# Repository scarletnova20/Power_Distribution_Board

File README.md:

# Power Distribution Board

Four-layer, 42 x 42 mm power distribution board for a 4S2P Li-ion system. The design combines a high-current ESC supply path, reverse-polarity protection, 5 V and 12 V auxiliary power interfaces, and analog/digital power telemetry.

> [!CAUTION]
> **This project is not fabrication-ready, and 50 A is a design target—not a tested current rating.** The current revision requires a non-standard mixed-copper stackup that has not been accepted by a fabricator. Thermal performance, current sharing, fuse coordination, wiring, BEC selection, and full-load operation also remain unqualified. Do not order boards or connect a high-current battery without completing the open release gates.

## Current design

The authoritative revision is in [`engineering/release50`](engineering/release50/):

- [`PDB_50A.kicad_pro`](engineering/release50/PDB_50A.kicad_pro) — KiCad project
- [`PDB_50A.kicad_sch`](engineering/release50/PDB_50A.kicad_sch) — schematic
- [`PDB_50A.kicad_pcb`](engineering/release50/PDB_50A.kicad_pcb) — PCB layout
- [`PDB_50A.kicad_dru`](engineering/release50/PDB_50A.kicad_dru) — design rules
- [`CONTINUATION.md`](engineering/release50/CONTINUATION.md) — latest engineering status and revision history
- [`fabrication_20260915/MANUFACTURING_SPEC.md`](engineering/release50/fabrication_20260915/MANUFACTURING_SPEC.md) — current vendor-neutral manufacturing requirements
- [`PDB_50A_DESIGN_RECORD.md`](engineering/release50/PDB_50A_DESIGN_RECORD.md) — detailed design record, interfaces, BOM review, and release gates

The root-level `Swayatt_PCB*` files and `engineering/release42` are earlier development revisions and are retained for traceability.

## Design summary

| Item | Current design |
| --- | --- |
| Board | 42 x 42 mm, nominal 1.6 mm, four copper layers |
| Battery | 4S2P Li-ion; 14.8 V nominal, 16.8 V maximum normal |
| Load target | 50 A aggregate, unqualified |
| Stackup | 1 oz outer / 2 oz inner copper; vendor acceptance required |
| Main protection | External fuse provision and LM74502-controlled parallel NMOS reverse-polarity stage |
| Main output | ESC battery interface |
| Auxiliary power | External 5 V and 12 V BEC interfaces; outputs must not be paralleled |
| Telemetry | INA169 analog current sensing and INA228 digital power monitoring |
| CAD format | KiCad 10.0 |

## Verification snapshot

The active September 15, 2026 revision records:

- zero ERC findings and zero unconnected items;
- zero DRC findings under the included 6 mil / 5 mil mixed-copper rule deck;
- 52 electrical invariants and nine additional checks passing;
- matching PCB/netlist pad assignments and verified manufacturing exports.

These checks establish internal design consistency only. They do **not** establish manufacturability, thermal safety, a 50 A rating, or production readiness. See [`verification.json`](engineering/release50/verification.json) and the latest status in [`CONTINUATION.md`](engineering/release50/CONTINUATION.md).

## Opening the project

1. Install KiCad 10.0 or a compatible newer version.
2. Clone this repository.
3. Open `engineering/release50/PDB_50A.kicad_pro`.
4. Keep the repository structure intact so the included symbol and footprint library tables resolve correctly.

Before modifying or exporting the board, read the latest continuation notes and manufacturing specification. Generated review packages are evidence artifacts, not approved fabrication releases.

## Repository layout

```text
engineering/release50/   Active 50 A-target design, checks, and review outputs
engineering/release42/   Previous 42 mm development revision
engineering/             Analysis, routing, rendering, and verification scripts
Swayatt_Local.pretty/    Project-specific KiCad footprints
Swayatt_Local.kicad_sym  Project-specific KiCad symbols
```

## License

Licensed under the [Apache License 2.0](LICENSE).

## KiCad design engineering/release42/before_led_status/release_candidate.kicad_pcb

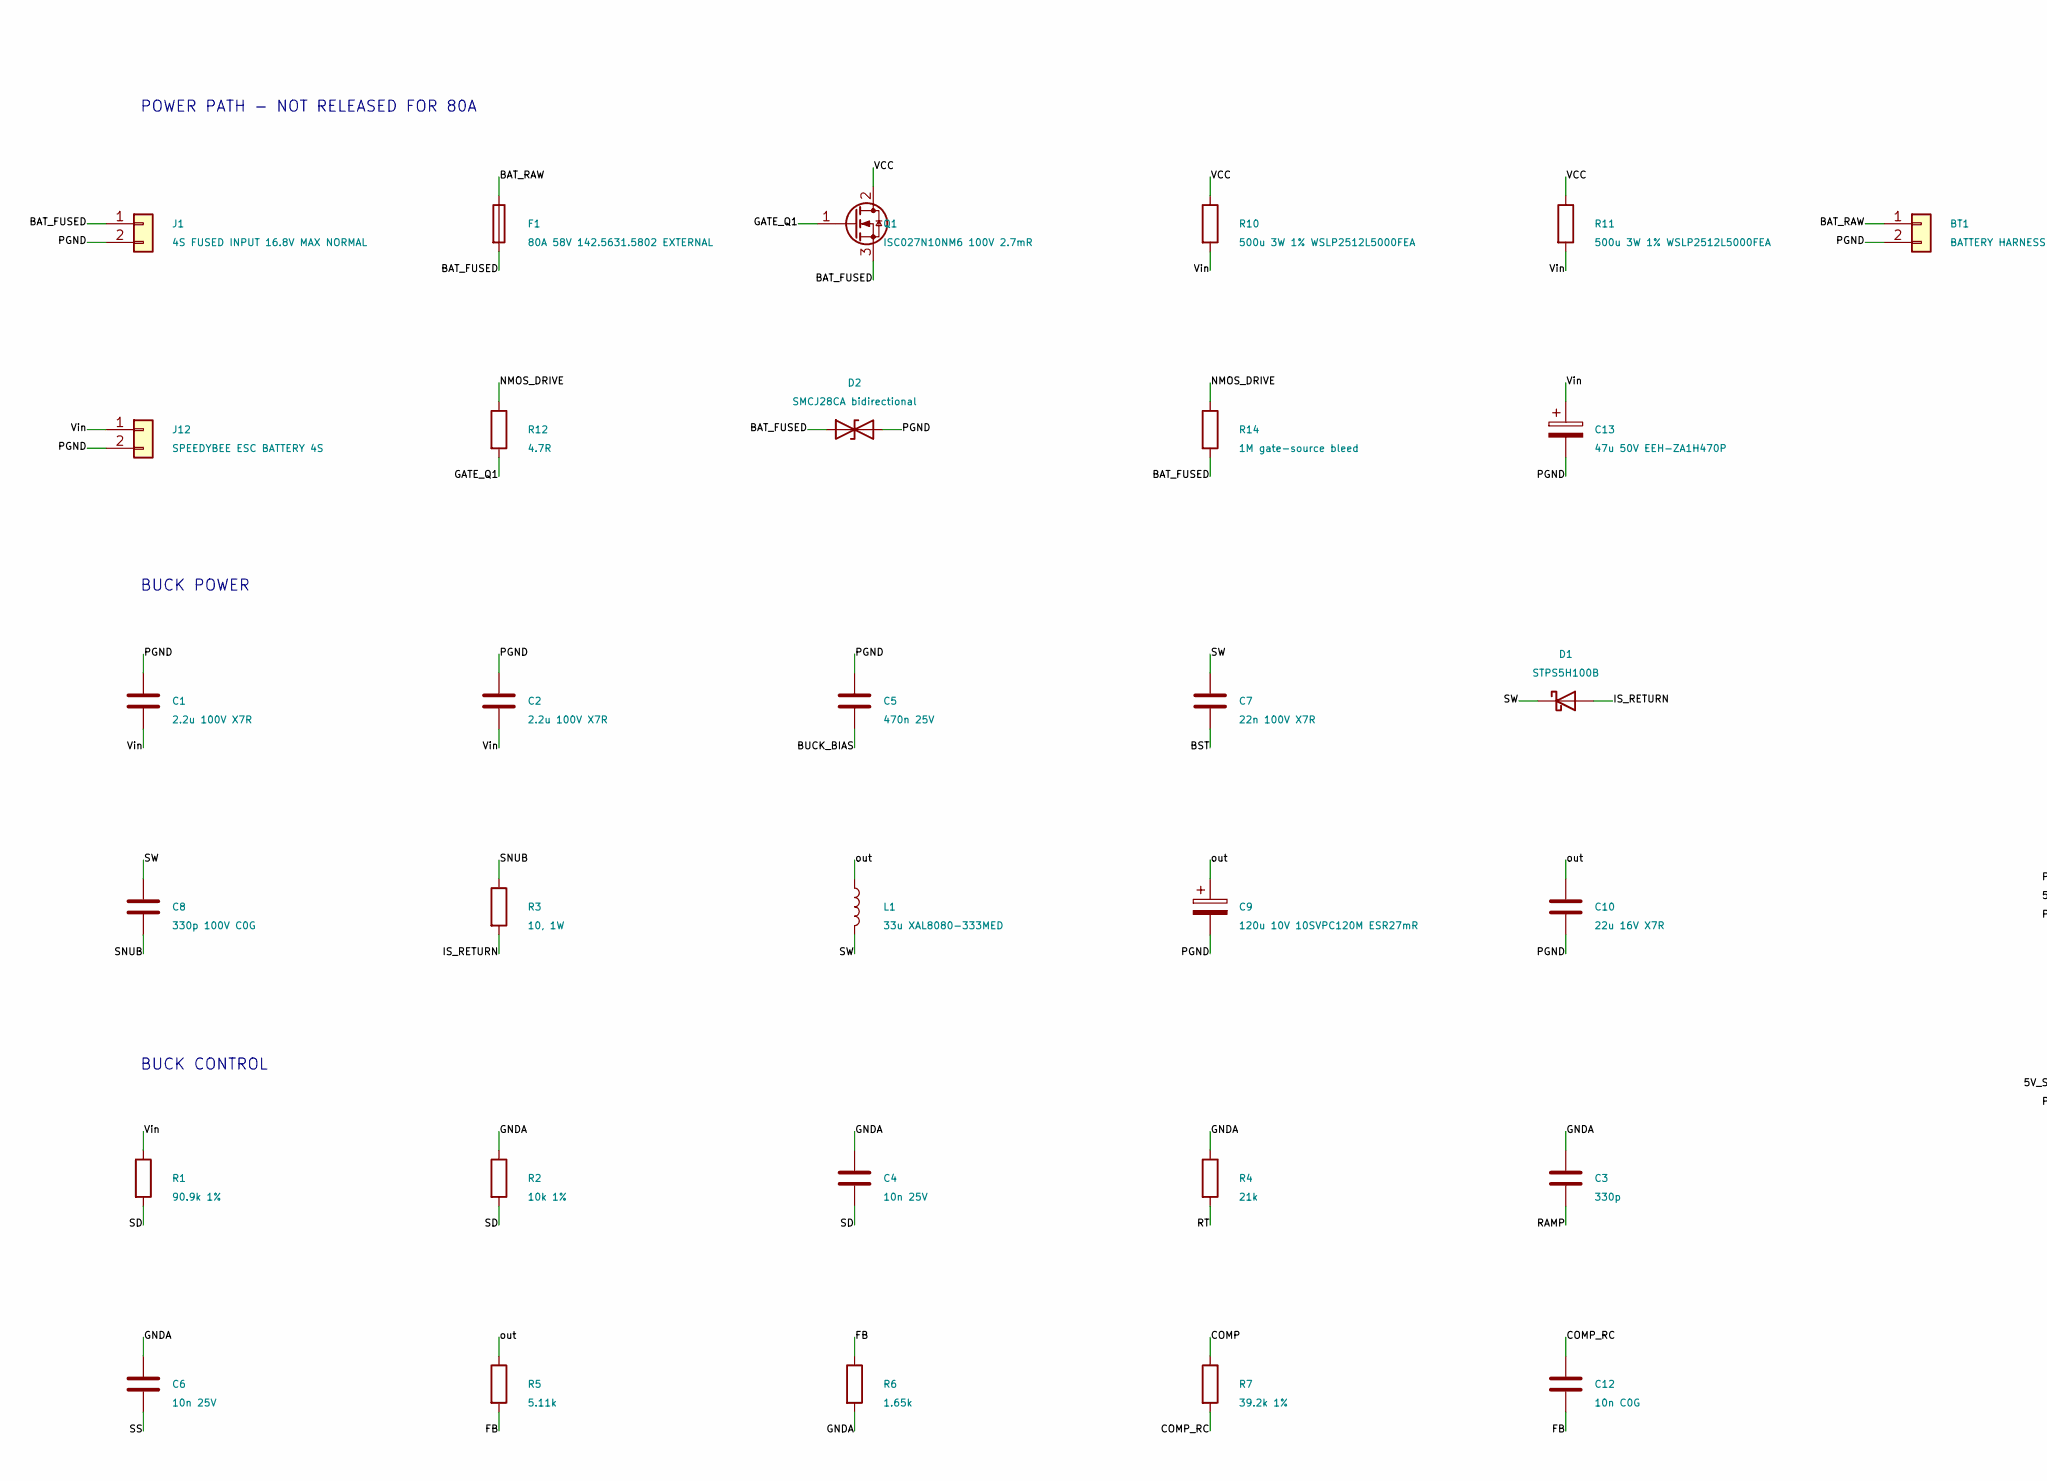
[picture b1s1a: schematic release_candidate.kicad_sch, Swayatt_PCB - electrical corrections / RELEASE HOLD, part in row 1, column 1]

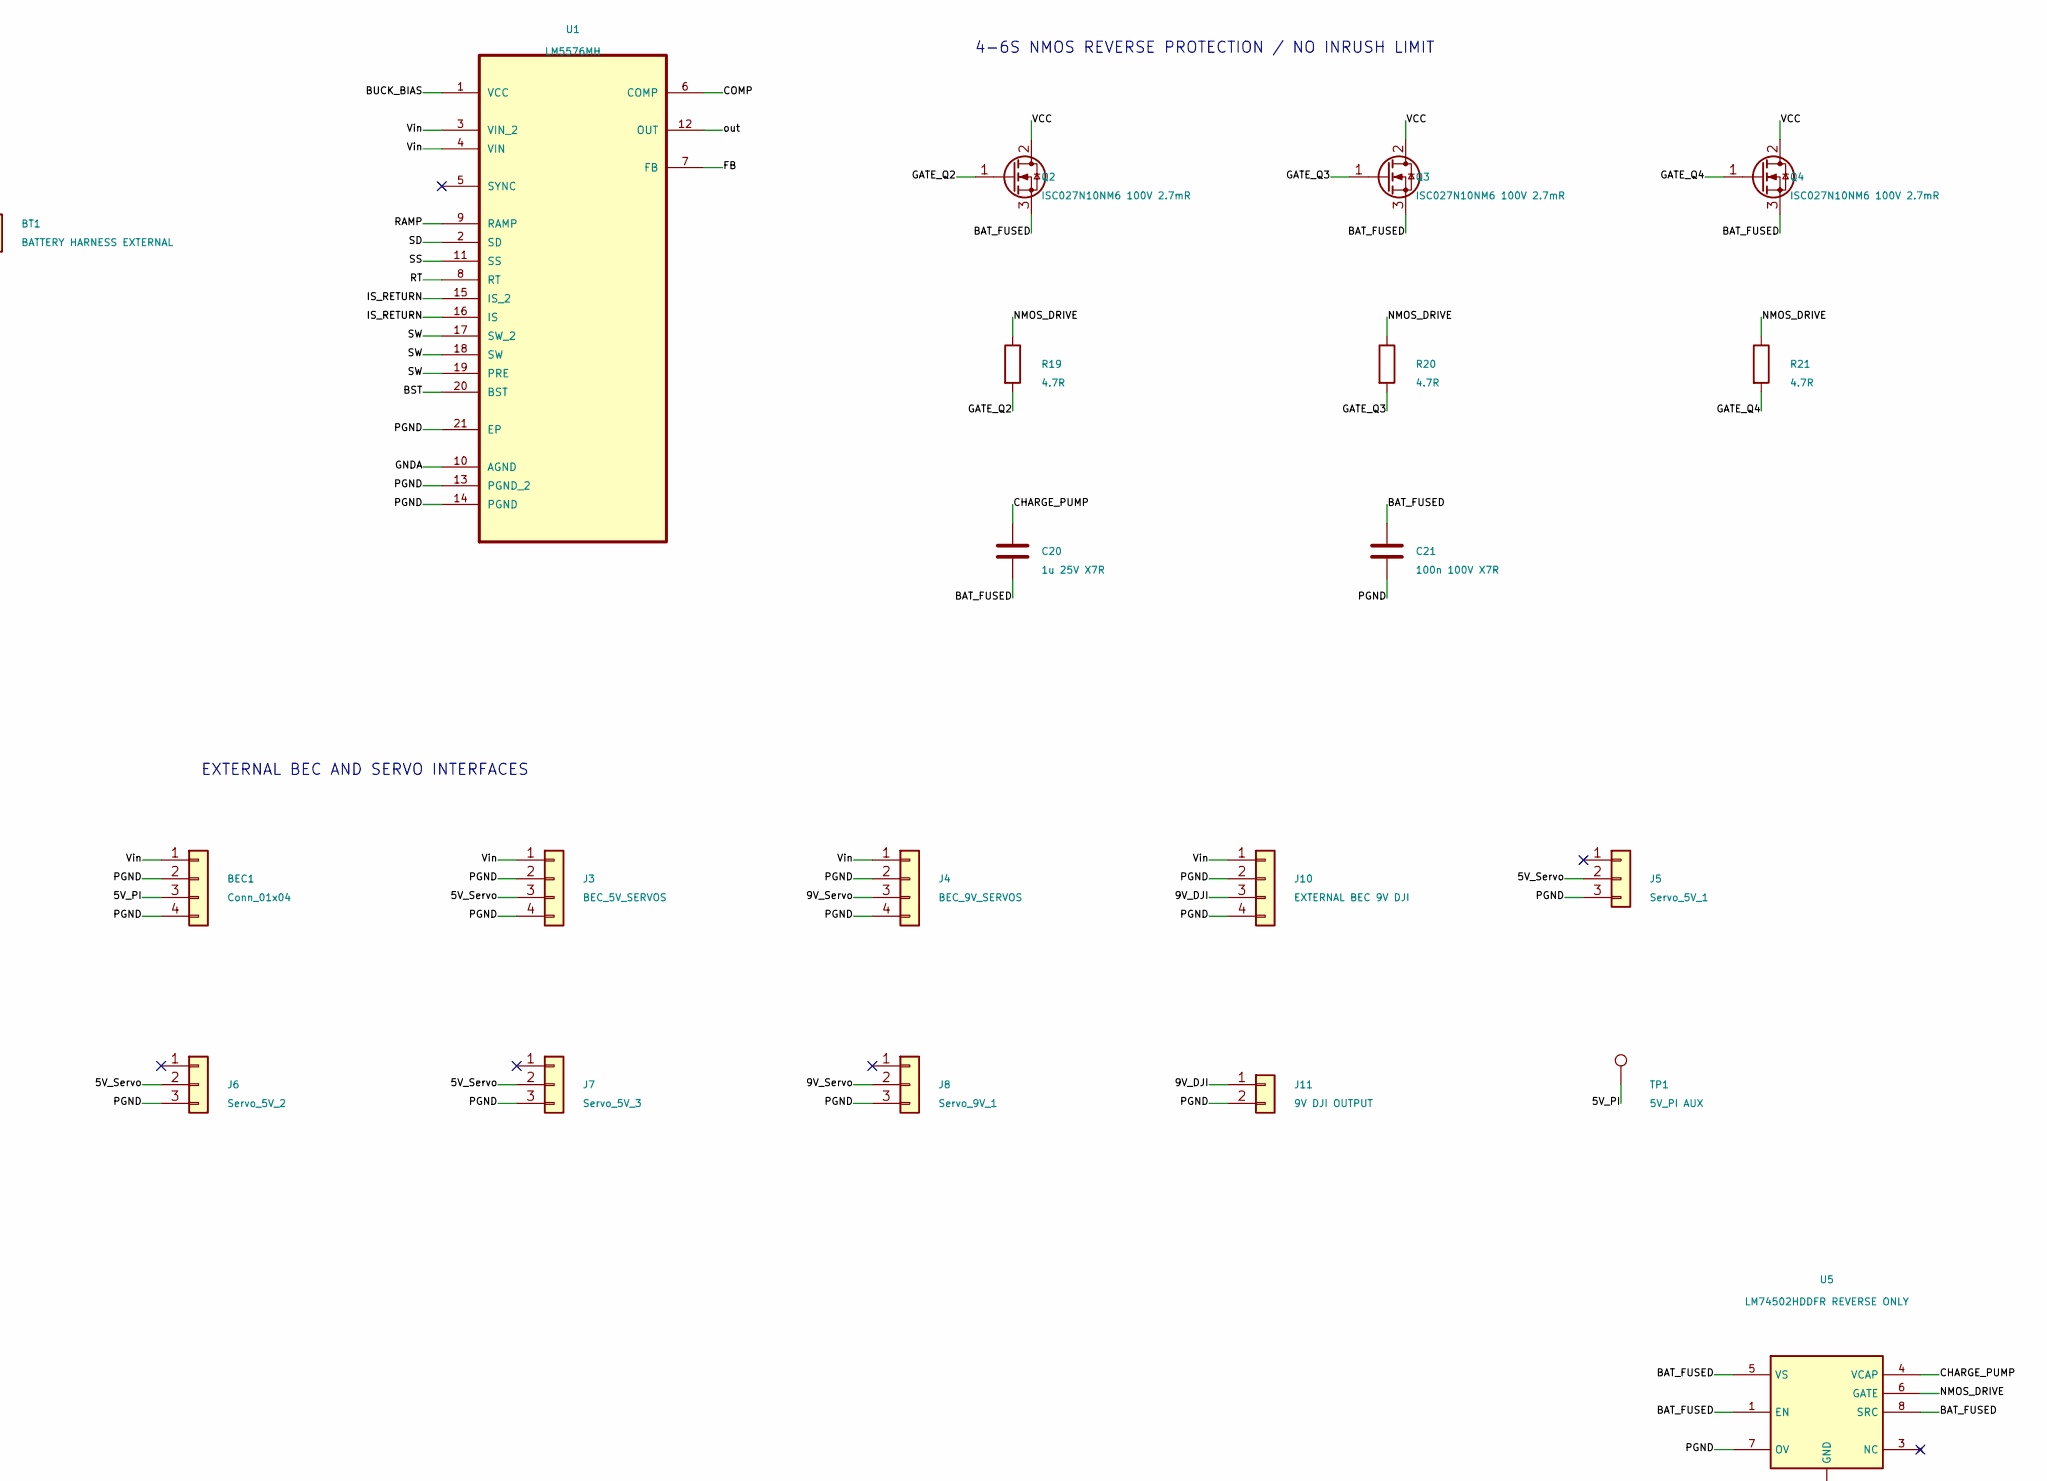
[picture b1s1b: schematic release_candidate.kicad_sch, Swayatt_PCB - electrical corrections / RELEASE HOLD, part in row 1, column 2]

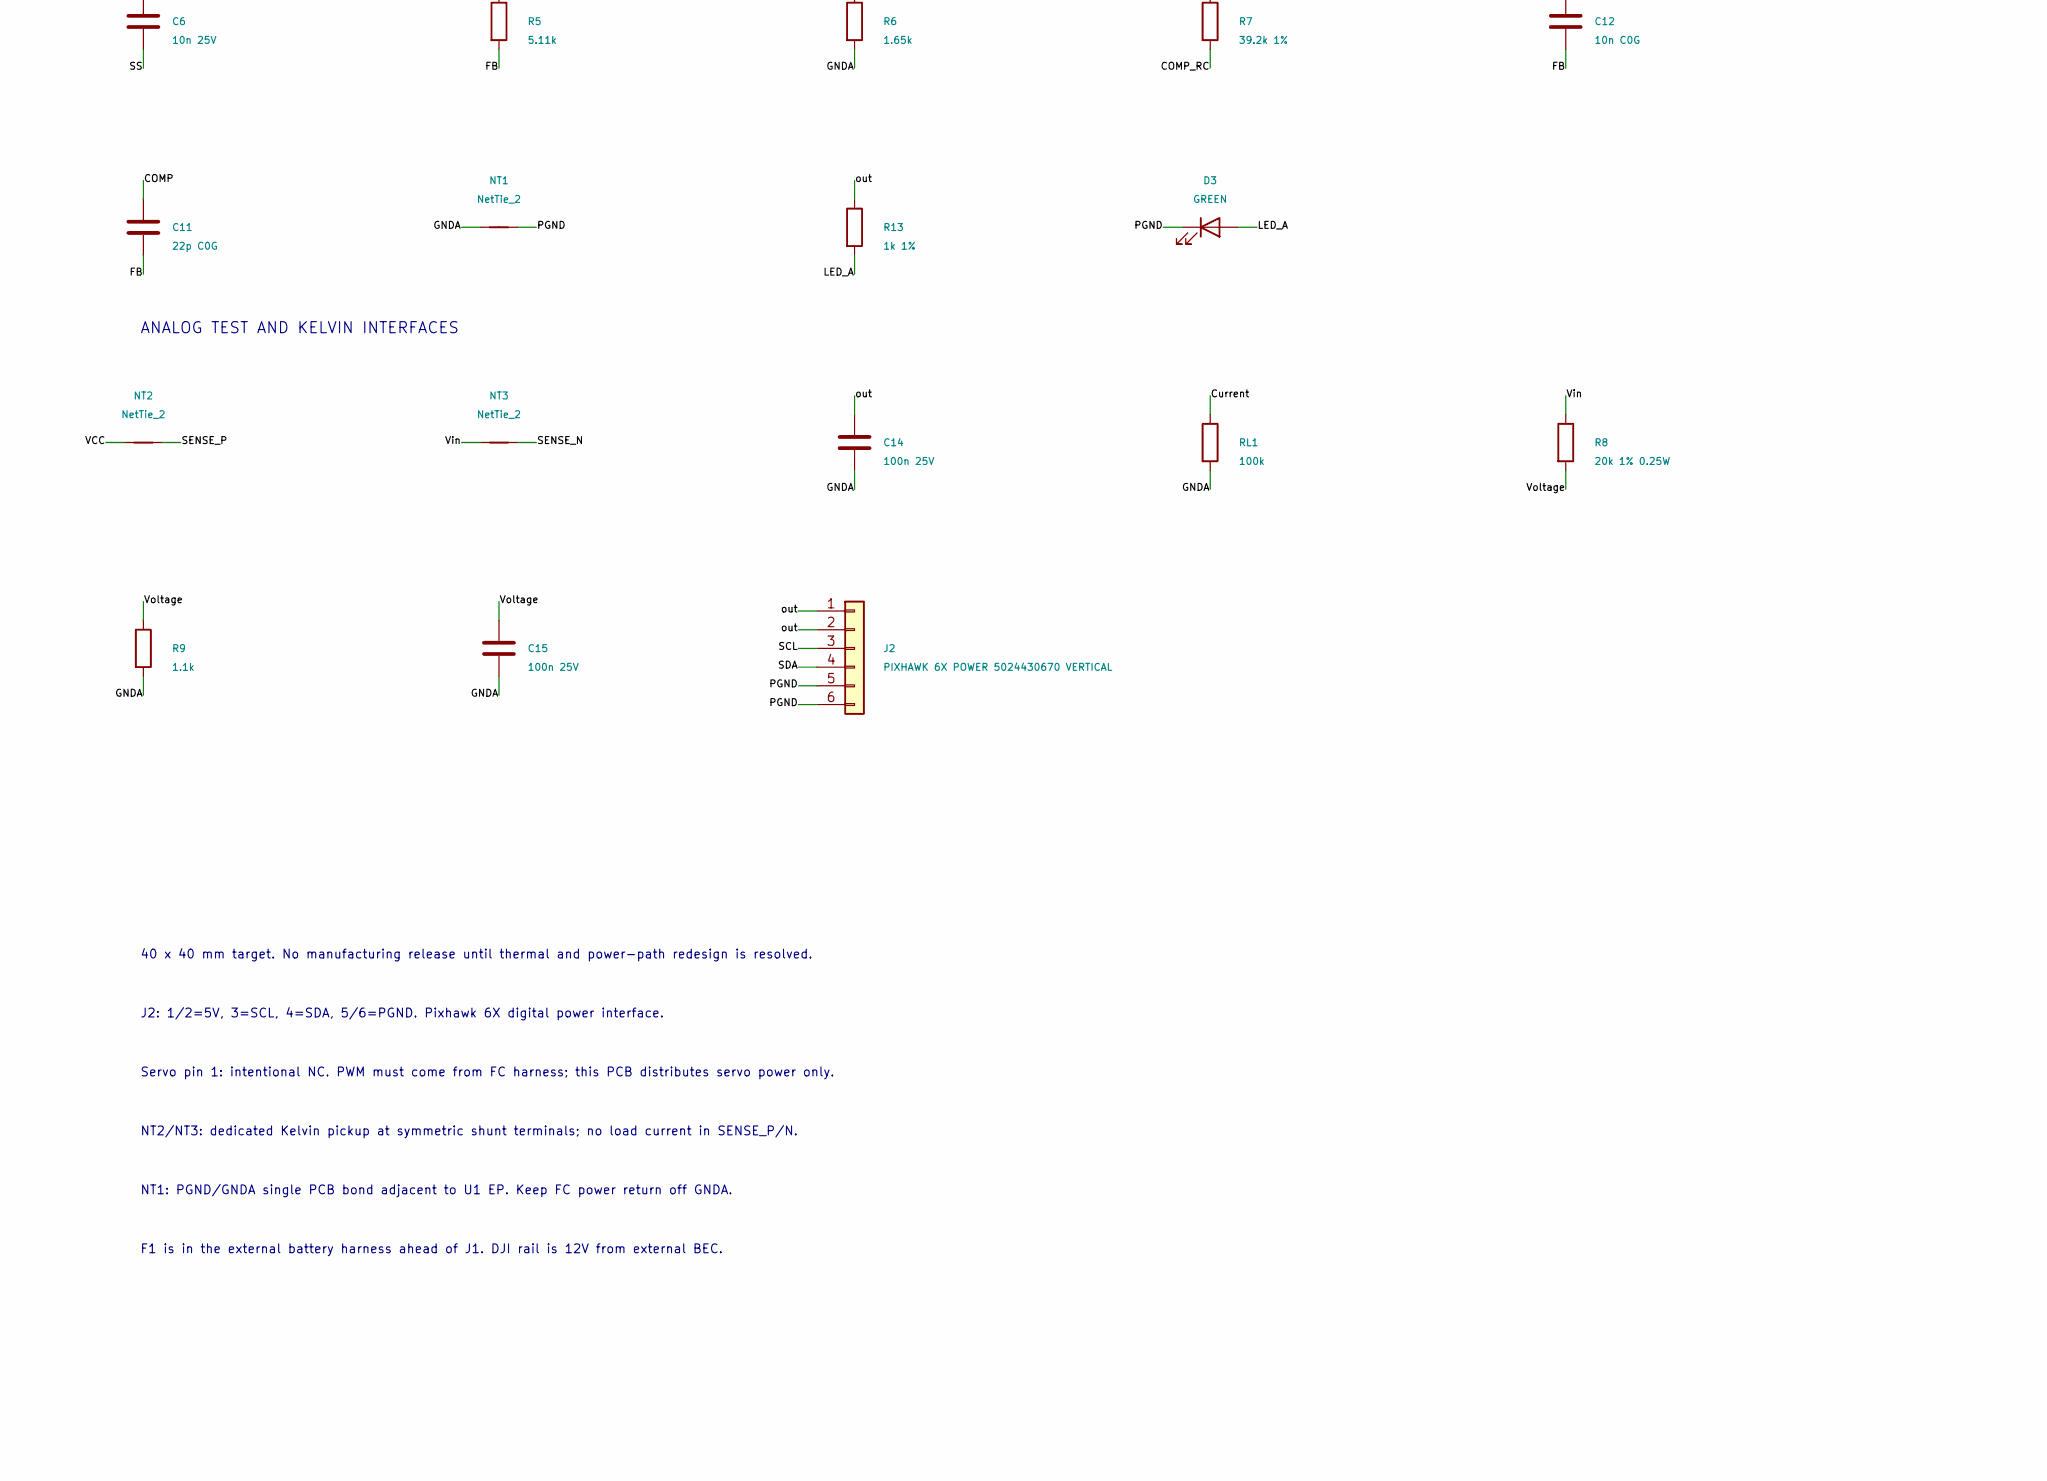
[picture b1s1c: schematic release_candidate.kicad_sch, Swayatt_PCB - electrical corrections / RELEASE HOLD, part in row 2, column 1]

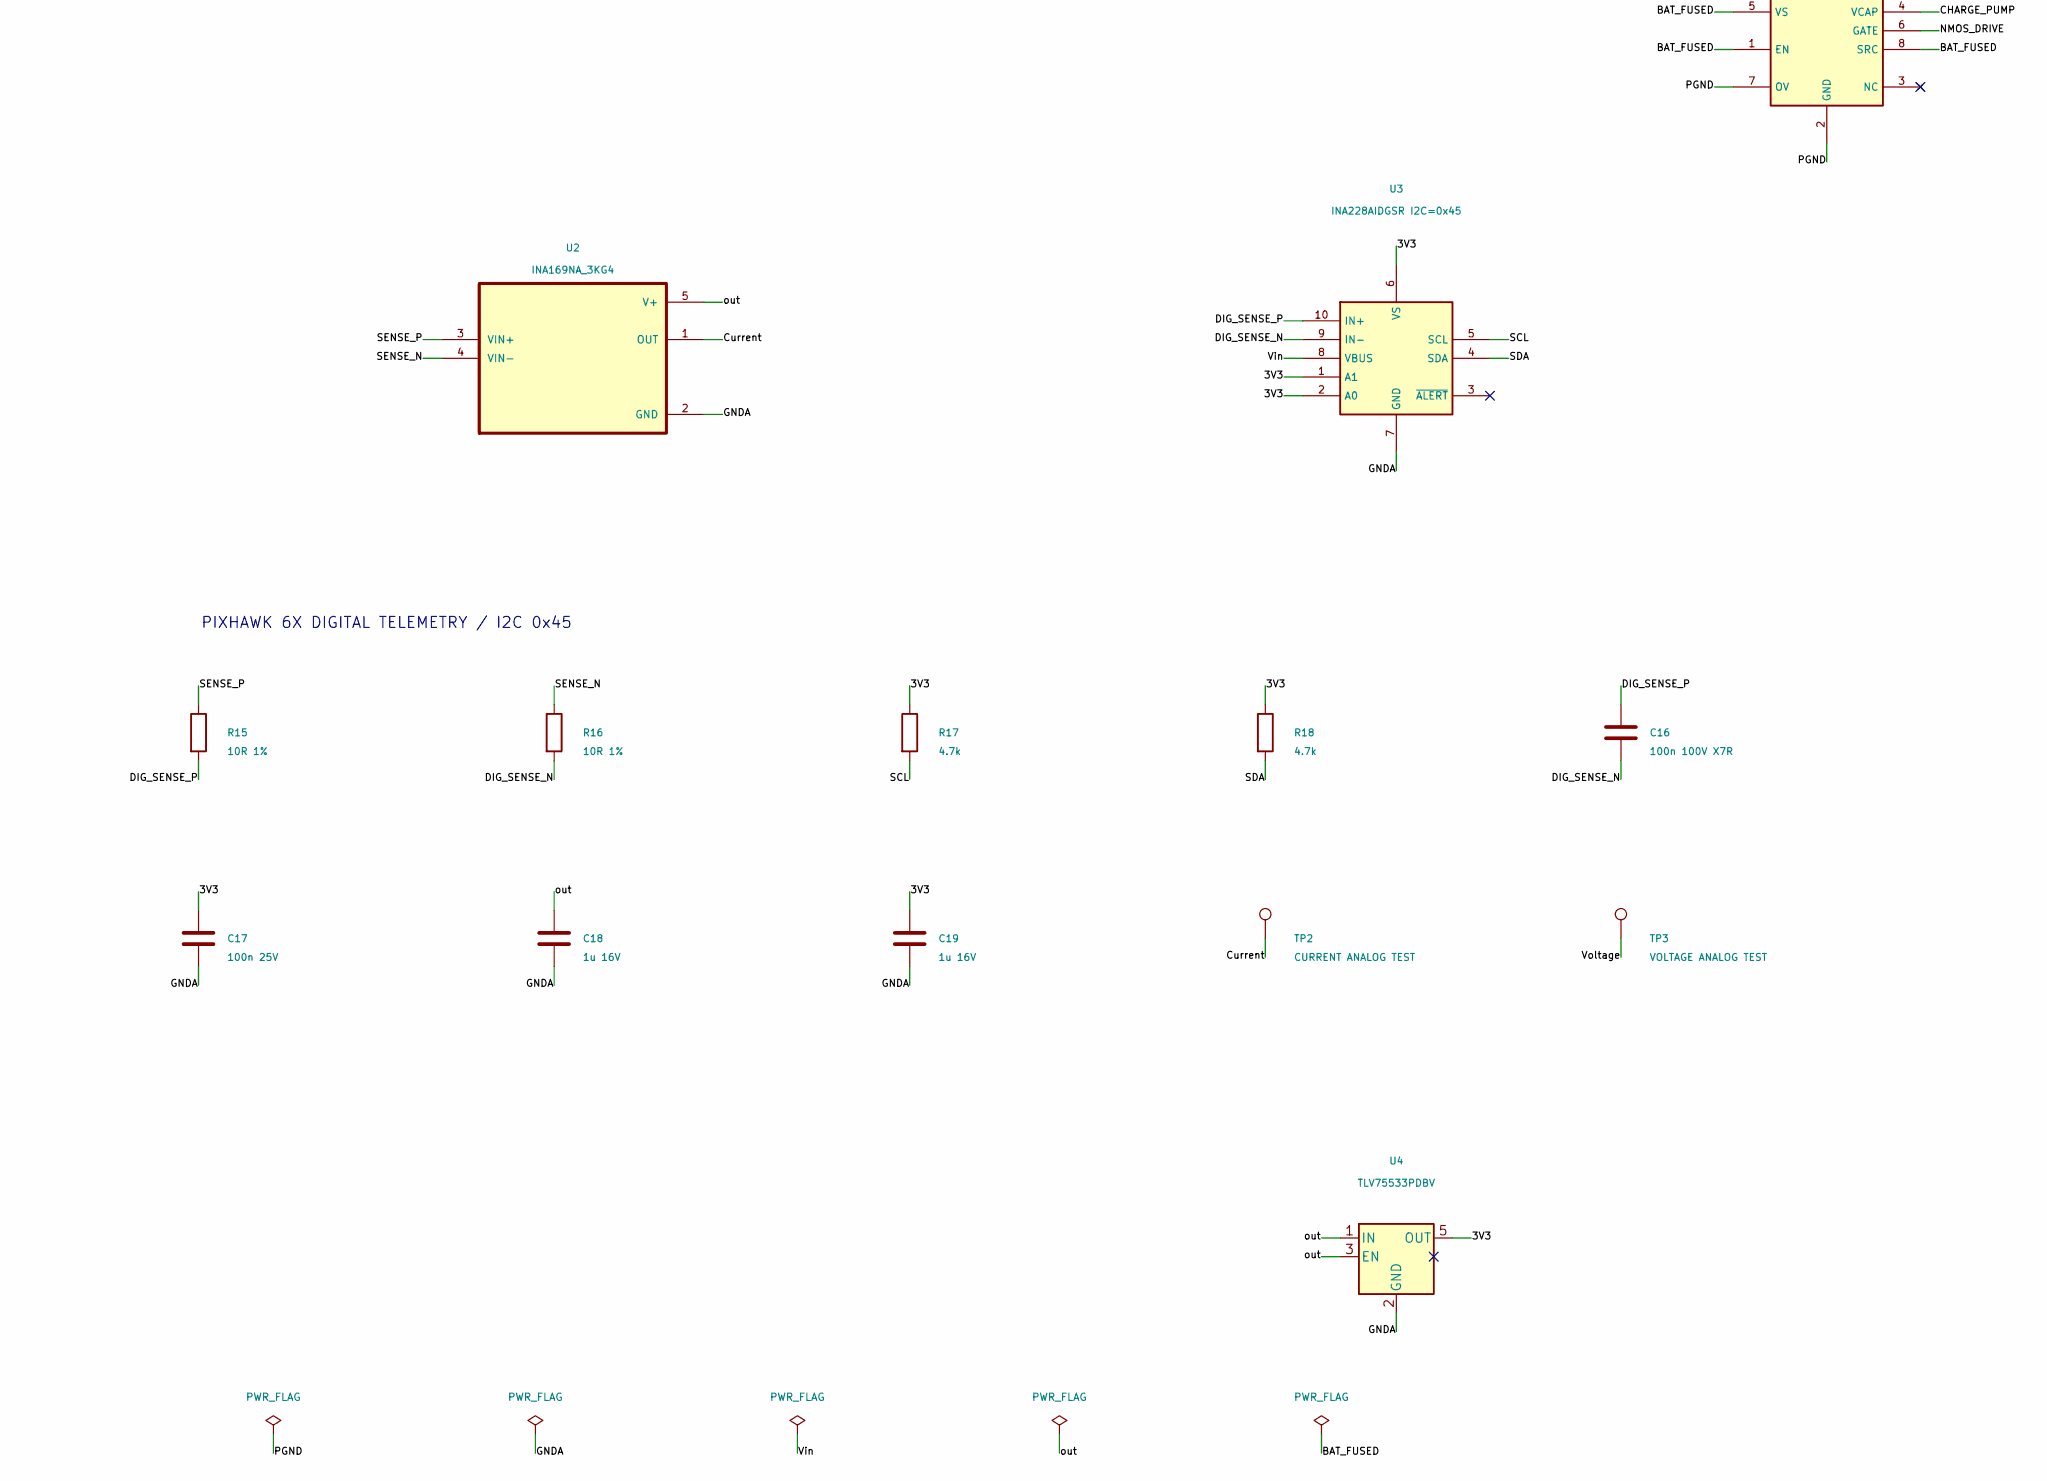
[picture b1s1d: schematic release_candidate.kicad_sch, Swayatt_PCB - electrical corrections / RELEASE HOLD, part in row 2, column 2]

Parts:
BEC1: Conn_01x04; BEC_Wire_4_42
BT1: BATTERY HARNESS EXTERNAL
C1, C2: 2.2u 100V X7R; C_1812_4532Metric
C3: 330p; C_0603_1608Metric
C4, C6: 10n 25V; C_0603_1608Metric
C5: 470n 25V; C_0603_1608Metric
C7: 22n 100V X7R; C_0805_2012Metric
C8: 330p 100V C0G; C_0805_2012Metric
C9: 120u 10V 10SVPC120M ESR27mR; Panasonic_OSCON_C6_10SVPC120M
C10: 22u 16V X7R; C_1206_3216Metric
C11: 22p C0G; C_0603_1608Metric
C12: 10n C0G; C_0603_1608Metric
C13: 47u 50V EEH-ZA1H470P; C_Elec_8x10.2
C14, C15, C17: 100n 25V; C_0603_1608Metric
C16, C21: 100n 100V X7R; C_0805_2012Metric
C18, C19: 1u 16V; C_0603_1608Metric
C20: 1u 25V X7R; C_0805_2012Metric
D1: STPS5H100B
D2: SMCJ28CA bidirectional; D_SMC
D3: GREEN; LED_0805_2012Metric
F1: 80A 58V 142.5631.5802 EXTERNAL
J1: 4S FUSED INPUT 16.8V MAX NORMAL; Power_Wire_2_42
J2: PIXHAWK 6X POWER 5024430670 VERTICAL; CLIK_Mate_502443_0670
J3: BEC_5V_SERVOS; BEC_Wire_4_42
J4: BEC_9V_SERVOS; BEC_Wire_4
J5: Servo_5V_1; PinHeader_1x03_P2.54mm_Vertical
J6: Servo_5V_2; PinHeader_1x03_P2.54mm_Vertical
J7: Servo_5V_3; PinHeader_1x03_P2.54mm_Vertical
J8: Servo_9V_1; PinHeader_1x03_P2.54mm_Vertical
J10: EXTERNAL BEC 9V DJI; BEC_Wire_4
J11: 9V DJI OUTPUT; Aux_Wire_2_42
J12: SPEEDYBEE ESC BATTERY 4S; Power_Wire_2_42
L1: 33u XAL8080-333MED; L_Coilcraft_XAL8080-XXX
NT1, NT2, NT3: NetTie_2; NetTie-2_SMD_Pad0.5mm
Q1, Q2, Q3, Q4: ISC027N10NM6 100V 2.7mR; ISC027N10NM6_GDS
R1: 90.9k 1%; R_0603_1608Metric
R2: 10k 1%; R_0603_1608Metric
R3: 10, 1W; R_2512_6332Metric
R4: 21k; R_0603_1608Metric
R5: 5.11k; R_0603_1608Metric
R6: 1.65k; R_0603_1608Metric
R7: 39.2k 1%; R_0603_1608Metric
R8: 20k 1% 0.25W; R_1206_3216Metric
R9: 1.1k; R_0603_1608Metric
R10, R11: 500u 3W 1% WSLP2512L5000FEA; WSLP2512_L5000
R12, R19, R20, R21: 4.7R; R_0603_1608Metric
R13: 1k 1%; R_0603_1608Metric
R14: 1M gate-source bleed; R_0603_1608Metric
R15, R16: 10R 1%; R_0603_1608Metric
R17, R18: 4.7k; R_0603_1608Metric
RL1: 100k; R_0603_1608Metric
TP1: 5V_PI AUX; TestPoint_Pad_D1.5mm
TP2: CURRENT ANALOG TEST; TestPoint_Pad_D1.5mm
TP3: VOLTAGE ANALOG TEST; TestPoint_Pad_D1.5mm
U1: LM5576MH; LM5576_PWP20; MPN LM5576MH
U2: INA169NA_3KG4; SOT-23-5
U3: INA228AIDGSR I2C=0x45; MSOP-10_3x3mm_P0.5mm
U4: TLV75533PDBV; SOT-23-5
U5: LM74502HDDFR REVERSE ONLY; LM74502_DDF8

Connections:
/3V3: C17.1, C19.1, R17.1, R18.1, U3.1 (A1), U3.2 (A0), U3.6 (VS), U4.5 (OUT)
/5V_PI: BEC1.3, TP1.1
/5V_Servo: J3.3, J5.2, J6.2, J7.2
/9V_DJI: J10.3, J11.1
/9V_Servo: J4.3, J8.2
/BAT_FUSED: C20.2, C21.1, D2.1 (A1), F1.2, J1.1, Q1.3 (S), Q2.3 (S), Q3.3 (S), Q4.3 (S), R14.2, U5.1 (EN), U5.5 (VS), U5.8 (SRC)
/BST: C7.2, U1.20 (BST)
/BUCK_BIAS: C5.2, U1.1 (VCC)
/CHARGE_PUMP: C20.1, U5.4 (VCAP)
/COMP: C11.1, R7.1, U1.6 (COMP)
/COMP_RC: C12.1, R7.2
/Current: RL1.1, TP2.1, U2.1 (OUT)
/DIG_SENSE_N: C16.2, R16.2, U3.9 (IN-)
/DIG_SENSE_P: C16.1, R15.2, U3.10 (IN+)
/FB: C11.2, C12.2, R5.2, R6.1, U1.7 (FB)
/GATE_Q1: Q1.1 (G), R12.2
/GATE_Q2: Q2.1 (G), R19.2
/GATE_Q3: Q3.1 (G), R20.2
/GATE_Q4: Q4.1 (G), R21.2
/GNDA: C3.1, C4.1, C6.1, C14.2, C15.2, C17.2, C18.2, C19.2, NT1.1, R2.1, R4.1, R6.2, R9.2, RL1.2, U1.10 (AGND), U2.2 (GND), U3.7 (GND), U4.2 (GND)
/IS_RETURN: D1.2 (A), R3.2, U1.15 (IS_2), U1.16 (IS)
/LED_A: D3.2 (A), R13.2
/NMOS_DRIVE: R12.1, R14.1, R19.1, R20.1, R21.1, U5.6 (GATE)
/PGND: BEC1.2, BEC1.4, BT1.2, C1.1, C2.1, C5.1, C9.2, C10.2, C13.2, C21.2, D2.2 (A2), D3.1 (K), J1.2, J2.5, J2.6, J3.2, J3.4, J4.2, J4.4, J5.3, J6.3, J7.3, J8.3, J10.2, J10.4, J11.2, J12.2, NT1.2, U1.13 (PGND_2), U1.14 (PGND), U1.21 (EP), U5.2 (GND), U5.7 (OV)
/RAMP: C3.2, U1.9 (RAMP)
/RT: R4.2, U1.8 (RT)
/SCL: J2.3, R17.2, U3.5 (SCL)
/SD: C4.2, R1.2, R2.2, U1.2 (SD)
/SDA: J2.4, R18.2, U3.4 (SDA)
/SENSE_N: NT3.2, R16.1, U2.4 (VIN-)
/SENSE_P: NT2.2, R15.1, U2.3 (VIN+)
/SNUB: C8.2, R3.1
/SS: C6.2, U1.11 (SS)
/SW: C7.1, C8.1, D1.1 (K), L1.2, U1.17 (SW_2), U1.18 (SW), U1.19 (PRE)
/VCC: NT2.1, Q1.2 (D), Q2.2 (D), Q3.2 (D), Q4.2 (D), R10.1, R11.1
/Vin: BEC1.1, C1.2, C2.2, C13.1, J3.1, J4.1, J10.1, J12.1, NT3.1, R1.1, R8.1, R10.2, R11.2, U1.3 (VIN_2), U1.4 (VIN), U3.8 (VBUS)
/Voltage: C15.1, R8.2, R9.1, TP3.1
/out: C9.1, C10.1, C14.1, C18.1, J2.1, J2.2, L1.1, R5.1, R13.1, U1.12 (OUT), U2.5 (V+), U4.1 (IN), U4.3 (EN)
unnamed: BT1.1, F1.1

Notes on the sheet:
POWER PATH - NOT RELEASED FOR 80A
BUCK POWER
BUCK CONTROL
ANALOG TEST AND KELVIN INTERFACES
EXTERNAL BEC AND SERVO INTERFACES
PIXHAWK 6X DIGITAL TELEMETRY / I2C 0x45
4-6S NMOS REVERSE PROTECTION / NO INRUSH LIMIT
40 x 40 mm target. No manufacturing release until thermal and power-path redesign is resolved.
J2: 1/2=5V, 3=SCL, 4=SDA, 5/6=PGND. Pixhawk 6X digital power interface.
Servo pin 1: intentional NC. PWM must come from FC harness; this PCB distributes servo power only.
NT2/NT3: dedicated Kelvin pickup at symmetric shunt terminals; no load current in SENSE_P/N.
NT1: PGND/GNDA single PCB bond adjacent to U1 EP. Keep FC power return off GNDA.
F1 is in the external battery harness ahead of J1. DJI rail is 12V from external BEC.

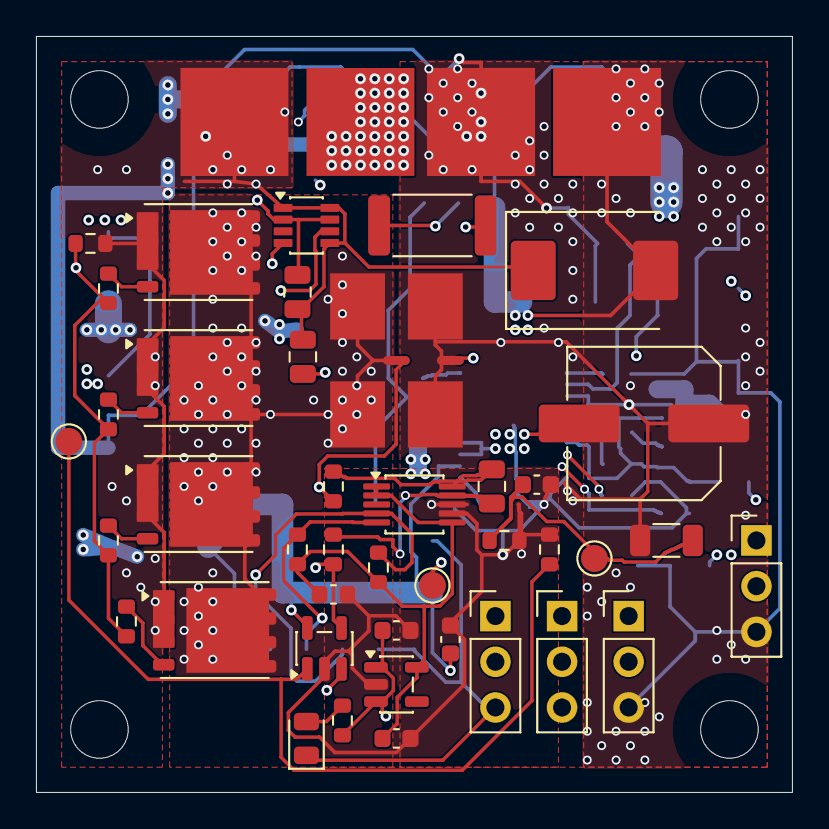
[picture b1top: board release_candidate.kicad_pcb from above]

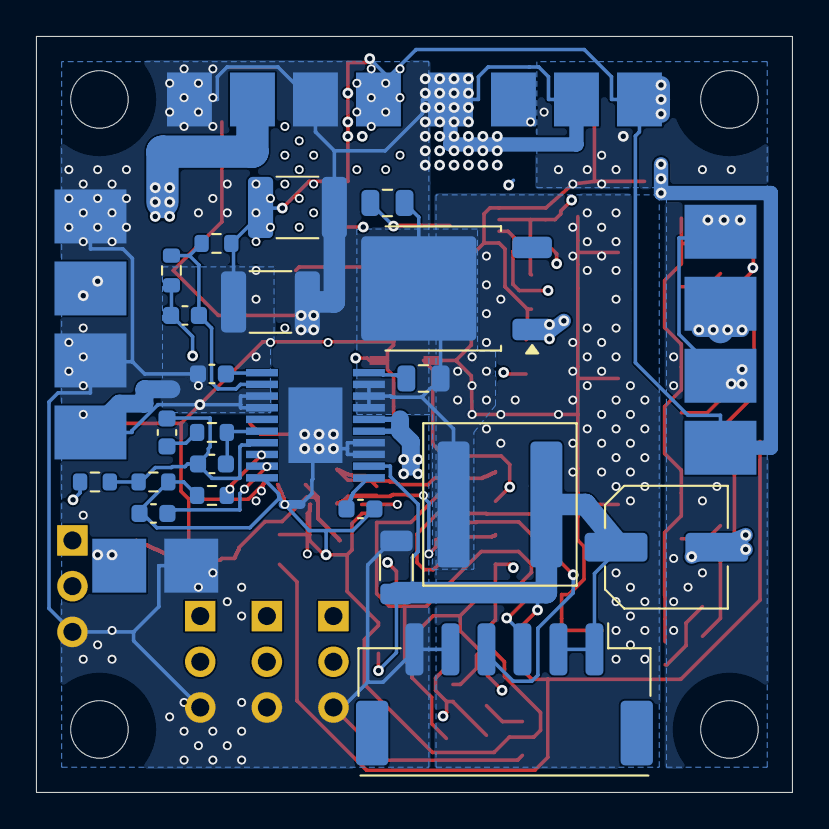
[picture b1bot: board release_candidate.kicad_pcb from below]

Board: 4 copper layers, 42.0 x 42.0 mm, 78 parts (28 on the bottom side), 38 nets.

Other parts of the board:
H1, H2, H3, H4: M3 3.2mm NPTH; MountingHole_3.2mm_M3

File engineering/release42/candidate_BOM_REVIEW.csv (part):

Reference,Schematic value,Footprint,Manufacturer,Verified ordering code,Status,Notes
BEC1,Conn_01x04,Swayatt_Local:BEC_Wire_4_42,,,NOT RELEASED,"External Pi BEC; PCB /5V_PI connection is a test-point branch, not the 5 A load path"
BT1,BATTERY HARNESS EXTERNAL,,,,NOT RELEASED,Exact ordering code/assembly specification requires BOM review
C1,2.2u 100V X7R,Capacitor_SMD:C_1812_4532Metric,,,NOT RELEASED,Exact MLCC and effective capacitance under DC bias must be verified
C10,22u 16V X7R,Capacitor_SMD:C_1206_3216Metric,,,NOT RELEASED,Exact MLCC and effective capacitance under DC bias must be verified
C11,22p C0G,Capacitor_SMD:C_0603_1608Metric,,,NOT RELEASED,Exact ordering code/assembly specification requires BOM review
C12,10n C0G,Capacitor_SMD:C_0603_1608Metric,,,NOT RELEASED,Exact ordering code/assembly specification requires BOM review
C13,47u 50V EEH-ZA1H470P,Capacitor_SMD:C_Elec_8x10.2,Panasonic,EEH-ZA1H470P,NOT RELEASED,SMD hybrid reservoir
C14,100n 25V,Capacitor_SMD:C_0603_1608Metric,,,NOT RELEASED,Exact ordering code/assembly specification requires BOM review
C15,100n 25V,Capacitor_SMD:C_0603_1608Metric,,,NOT RELEASED,Exact ordering code/assembly specification requires BOM review
C16,100n 100V X7R,Capacitor_SMD:C_0805_2012Metric,,,NOT RELEASED,Exact ordering code/assembly specification requires BOM review
C17,100n 25V,Capacitor_SMD:C_0603_1608Metric,,,NOT RELEASED,Exact ordering code/assembly specification requires BOM review
C18,1u 16V,Capacitor_SMD:C_0603_1608Metric,,,NOT RELEASED,Exact ordering code/assembly specification requires BOM review
C19,1u 16V,Capacitor_SMD:C_0603_1608Metric,,,NOT RELEASED,Exact ordering code/assembly specification requires BOM review
C2,2.2u 100V X7R,Capacitor_SMD:C_1812_4532Metric,,,NOT RELEASED,Exact MLCC and effective capacitance under DC bias must be verified
C20,1u 25V X7R,Capacitor_SMD:C_0805_2012Metric,,,NOT RELEASED,Exact ordering code/assembly specification requires BOM review
C21,100n 100V X7R,Capacitor_SMD:C_0805_2012Metric,,,NOT RELEASED,Exact ordering code/assembly specification requires BOM review
C3,330p,Capacitor_SMD:C_0603_1608Metric,,,NOT RELEASED,Exact ordering code/assembly specification requires BOM review
C4,10n 25V,Capacitor_SMD:C_0603_1608Metric,,,NOT RELEASED,Exact ordering code/assembly specification requires BOM review
C5,470n 25V,Capacitor_SMD:C_0603_1608Metric,,,NOT RELEASED,Exact ordering code/assembly specification requires BOM review
C6,10n 25V,Capacitor_SMD:C_0603_1608Metric,,,NOT RELEASED,Exact ordering code/assembly specification requires BOM review
C7,22n 100V X7R,Capacitor_SMD:C_0805_2012Metric,,,NOT RELEASED,Exact ordering code/assembly specification requires BOM review
C8,330p 100V C0G,Capacitor_SMD:C_0805_2012Metric,,,NOT RELEASED,Exact ordering code/assembly specification requires BOM review
C9,120u 10V 10SVPC120M ESR27mR,Swayatt_Local:Panasonic_OSCON_C6_10SVPC120M,Panasonic,10SVPC120M,NOT RELEASED,Manufacturer C6 land pattern applied
D1,STPS5H100B,Swayatt_Local:STPS5H100B,,,NOT RELEASED,Exact ordering code/assembly specification requires BOM review
D2,SMCJ28CA bidirectional,Diode_SMD:D_SMC,,,NOT RELEASED,Existing SMCJ28CA; 4S clamp selection and pulse-current path not qualified
D3,GREEN 5V ON,LED_SMD:LED_0805_2012Metric,,,NOT RELEASED,Exact ordering code/assembly specification requires BOM review
F1,80A 58V 142.5631.5802 EXTERNAL,,,,NOT RELEASED,Exact ordering code/assembly specification requires BOM review
J1,4S FUSED INPUT 16.8V MAX NORMAL,Swayatt_Local:Power_Wire_2_42,,,NOT RELEASED,Exact ordering code/assembly specification requires BOM review
J10,EXTERNAL BEC 9V DJI,Swayatt_Local:BEC_Wire_4,,,NOT RELEASED,Exact ordering code/assembly specification requires BOM review
J11,9V DJI OUTPUT,Swayatt_Local:Aux_Wire_2_42,,,NOT RELEASED,Exact ordering code/assembly specification requires BOM review
J12,SPEEDYBEE ESC BATTERY 4S,Swayatt_Local:Power_Wire_2_42,,,NOT RELEASED,Exact ordering code/assembly specification requires BOM review
J2,PIXHAWK 6X POWER 5024430670 VERTICAL,Swayatt_Local:CLIK_Mate_502443_0670,,,NOT RELEASED,Exact ordering code/assembly specification requires BOM review
J3,BEC_5V_SERVOS,Swayatt_Local:BEC_Wire_4_42,,,NOT RELEASED,Exact ordering code/assembly specification requires BOM review
J4,BEC_9V_SERVOS,Swayatt_Local:BEC_Wire_4,,,NOT RELEASED,Exact ordering code/assembly specification requires BOM review
J5,Servo_5V_1,Connector_PinHeader_2.54mm:PinHeader_1x03_P2.54mm_Vertical,,,NOT RELEASED,Exact ordering code/assembly specification requires BOM review
J6,Servo_5V_2,Connector_PinHeader_2.54mm:PinHeader_1x03_P2.54mm_Vertical,,,NOT RELEASED,Exact ordering code/assembly specification requires BOM review
J7,Servo_5V_3,Connector_PinHeader_2.54mm:PinHeader_1x03_P2.54mm_Vertical,,,NOT RELEASED,Exact ordering code/assembly specification requires BOM review
J8,Servo_9V_1,Connector_PinHeader_2.54mm:PinHeader_1x03_P2.54mm_Vertical,,,NOT RELEASED,Exact ordering code/assembly specification requires BOM review
L1,33u XAL8080-333MED,Inductor_SMD:L_Coilcraft_XAL8080-XXX,Coilcraft,XAL8080-333MED,NOT RELEASED,33 uH; manufacturer electrical data reviewed
NT1,NetTie_2,NetTie:NetTie-2_SMD_Pad0.5mm,,,NOT RELEASED,Exact ordering code/assembly specification requires BOM review
NT2,NetTie_2,NetTie:NetTie-2_SMD_Pad0.5mm,,,NOT RELEASED,Exact ordering code/assembly specification requires BOM review
NT3,NetTie_2,NetTie:NetTie-2_SMD_Pad0.5mm,,,NOT RELEASED,Exact ordering code/assembly specification requires BOM review
Q1,ISC027N10NM6 100V 2.7mR,Swayatt_Local:ISC027N10NM6_GDS,,,NOT RELEASED,Exact ordering code/assembly specification requires BOM review
Q2,ISC027N10NM6 100V 2.7mR,Swayatt_Local:ISC027N10NM6_GDS,,,NOT RELEASED,Exact ordering code/assembly specification requires BOM review
Q3,ISC027N10NM6 100V 2.7mR,Swayatt_Local:ISC027N10NM6_GDS,,,NOT RELEASED,Exact ordering code/assembly specification requires BOM review
Q4,ISC027N10NM6 100V 2.7mR,Swayatt_Local:ISC027N10NM6_GDS,,,NOT RELEASED,Exact ordering code/assembly specification requires BOM review
R1,90.9k 1%,Resistor_SMD:R_0603_1608Metric,,,NOT RELEASED,Exact ordering code/assembly specification requires BOM review
R10,500u 3W 1% WSLP2512L5000FEA,Swayatt_Local:WSLP2512_L5000,Vishay,WSLP2512L5000FEA,NOT RELEASED,Kelvin pickup/current sharing review remains open
R11,500u 3W 1% WSLP2512L5000FEA,Swayatt_Local:WSLP2512_L5000,Vishay,WSLP2512L5000FEA,NOT RELEASED,Kelvin pickup/current sharing review remains open
R12,4.7R,Resistor_SMD:R_0603_1608Metric,,,NOT RELEASED,Exact ordering code/assembly specification requires BOM review
R13,1k 1%,Resistor_SMD:R_0603_1608Metric,,,NOT RELEASED,Exact ordering code/assembly specification requires BOM review
R14,1M gate-source bleed,Resistor_SMD:R_0603_1608Metric,,,NOT RELEASED,Exact ordering code/assembly specification requires BOM review
R15,10R 1%,Resistor_SMD:R_0603_1608Metric,,,NOT RELEASED,Exact ordering code/assembly specification requires BOM review
R16,10R 1%,Resistor_SMD:R_0603_1608Metric,,,NOT RELEASED,Exact ordering code/assembly specification requires BOM review
R17,4.7k,Resistor_SMD:R_0603_1608Metric,,,NOT RELEASED,Exact ordering code/assembly specification requires BOM review
R18,4.7k,Resistor_SMD:R_0603_1608Metric,,,NOT RELEASED,Exact ordering code/assembly specification requires BOM review
R19,4.7R,Resistor_SMD:R_0603_1608Metric,,,NOT RELEASED,Exact ordering code/assembly specification requires BOM review
R2,10k 1%,Resistor_SMD:R_0603_1608Metric,,,NOT RELEASED,Exact ordering code/assembly specification requires BOM review
R20,4.7R,Resistor_SMD:R_0603_1608Metric,,,NOT RELEASED,Exact ordering code/assembly specification requires BOM review
R21,4.7R,Resistor_SMD:R_0603_1608Metric,,,NOT RELEASED,Exact ordering code/assembly specification requires BOM review
R3,"10, 1W",Resistor_SMD:R_2512_6332Metric,,,NOT RELEASED,Exact ordering code/assembly specification requires BOM review
R4,21k,Resistor_SMD:R_0603_1608Metric,,,NOT RELEASED,Exact ordering code/assembly specification requires BOM review
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
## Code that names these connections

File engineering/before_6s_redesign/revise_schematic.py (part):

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symbols={prop(s,'Reference')[2]:deepcopy(s) for s in children(root,'symbol') if not prop(s,'Reference')[2].startswith('#')}
nl=ET.parse(base/'netlist.xml').getroot()
nets={}
renames={'GND':'PGND','Net-(D1-K)':'SW','Net-(U1-SW)':'SW','Net-(U1-VCC)':'BUCK_BIAS','Net-(J1-Pin_1)':'BAT_RAW','Net-(Q1-D)':'BAT_FUSED','Net-(Q1-G)':'PMOS_GATE','Net-(C8-Pad2)':'SNUB','Net-(C12-Pad1)':'COMP_RC'}
renamed_sources={}
for n in nl.find('nets'):
    name=n.attrib['name']; name=renames.get(name,name.removeprefix('/'))
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    symbols[ref]=s
    return s

# Datasheet pin functions; OUT is a voltage-sense input despite the table's O tag.
u=libs[one(symbols['U1'],'lib_id')[1]]
types={'1':'power_out','3':'power_in','4':'power_in','7':'input','9':'output','10':'power_in','11':'output','12':'input','13':'power_in','14':'power_in','17':'power_out','18':'passive','21':'power_in'}
for sub in children(u,'symbol'):
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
